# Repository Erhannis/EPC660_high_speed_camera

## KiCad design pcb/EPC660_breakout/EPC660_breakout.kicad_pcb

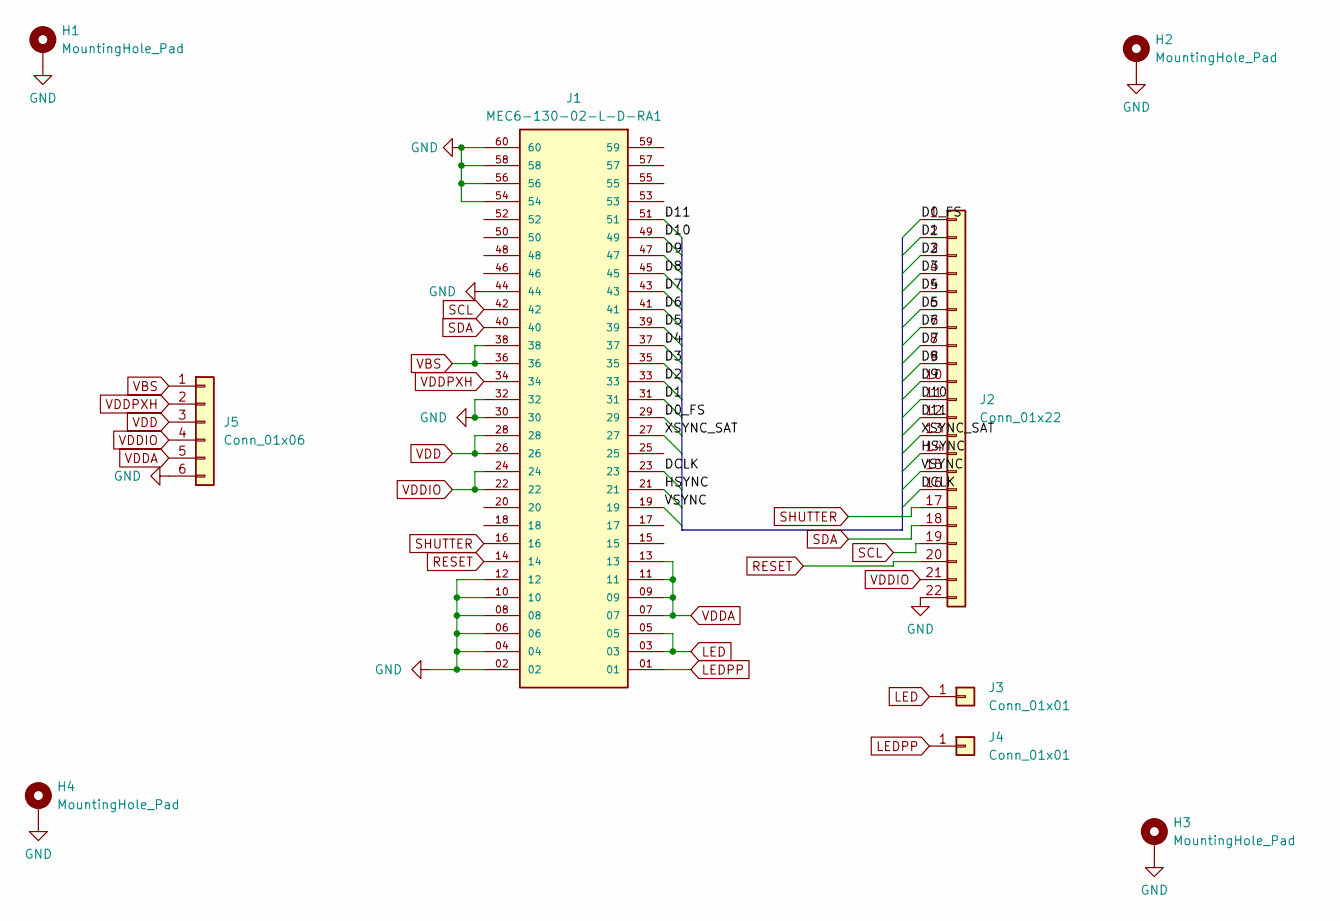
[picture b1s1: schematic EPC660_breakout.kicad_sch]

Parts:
H1, H2, H3, H4: MountingHole_Pad; MountingHole_2.5mm_Pad
J1: MEC6-130-02-L-D-RA1; SAMTEC_MEC6-130-02-L-D-RA1; PARTREV E
J2: Conn_01x22; PinHeader_1x22_P2.54mm_Vertical
J3, J4: Conn_01x01; PinHeader_1x01_P2.54mm_Vertical
J5: Conn_01x06; PinHeader_1x06_P2.54mm_Vertical

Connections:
/D0_FS: J1.29, J2.1
/D1: J1.31, J2.2
/D2: J1.33, J2.3
/D3: J1.35, J2.4
/D4: J1.37, J2.5
/D5: J1.39, J2.6
/D6: J1.41, J2.7
/D7: J1.43, J2.8
/D8: J1.45, J2.9
/D9: J1.47, J2.10
/D10: J1.49, J2.11
/D11: J1.51, J2.12
/DCLK: J1.23, J2.16
/HSYNC: J1.21, J2.14
/VSYNC: J1.19, J2.15
/XSYNC_SAT: J1.27, J2.13
GND: H1.1, H2.1, H3.1, H4.1, J1.02, J1.04, J1.06, J1.08, J1.10, J1.12, J1.30, J1.32, J1.44, J1.54, J1.56, J1.58, J1.60, J2.22, J5.6
LED: J1.03, J1.05, J3.1
LEDPP: J1.01, J4.1
RESET: J1.14, J2.20
SCL: J1.42, J2.19
SDA: J1.40, J2.18
SHUTTER: J1.16, J2.17
VBS: J1.36, J1.38, J5.1
VDD: J1.26, J1.28, J5.3
VDDA: J1.07, J1.09, J1.11, J1.13, J5.5
VDDIO: J1.22, J1.24, J2.21, J5.4
VDDPXH: J1.34, J5.2

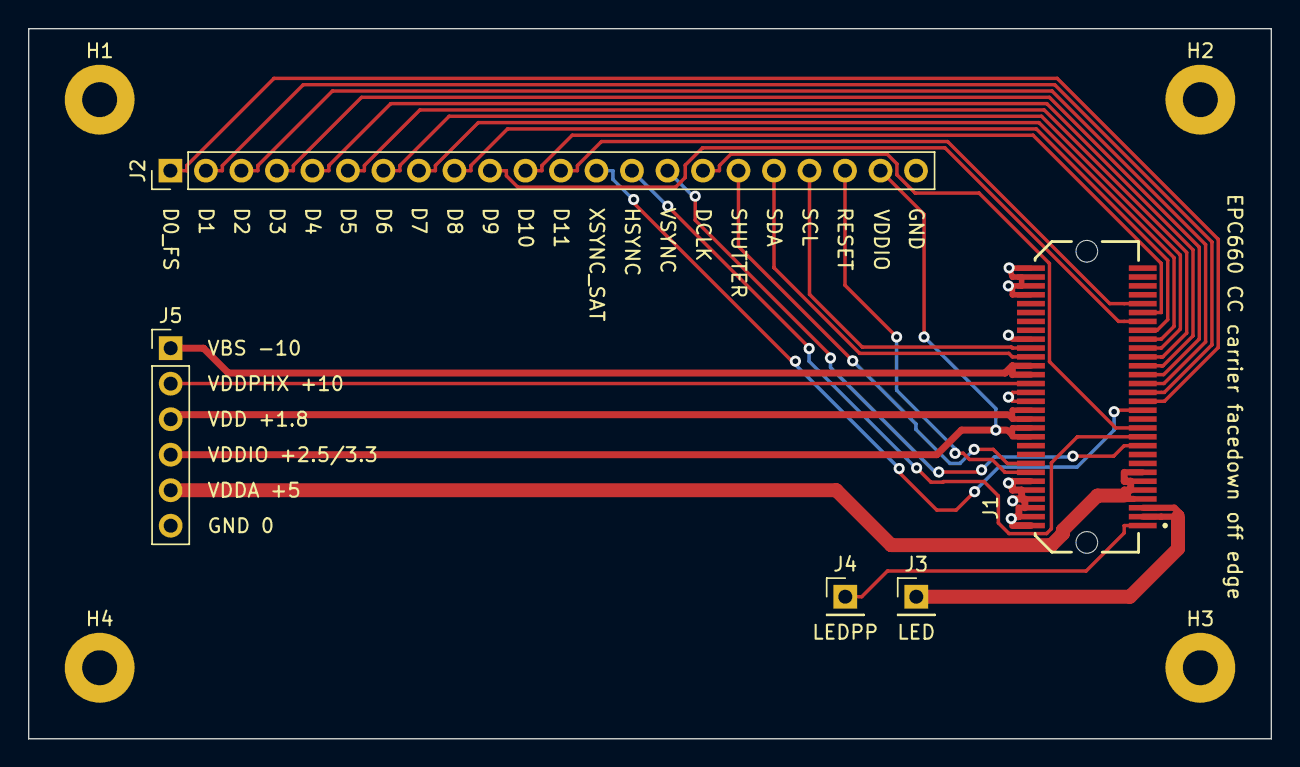
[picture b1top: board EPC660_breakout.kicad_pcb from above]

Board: 2 copper layers, 88.9 x 50.8 mm, 9 parts (0 on the bottom side), 28 nets.

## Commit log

2023-07-14 Initial commit. EPC660 CC Carrier breakout.
2023-07-14 Oh right, the ground plane.
2023-07-14 Also labels
2023-07-14 After deliberation, I increased trace widths proportional to the cardinality of the pin groups they ran to.
2023-07-14 Added bird
2023-07-14 Passes DRC
2023-07-14 Git hash
2023-07-14 OH DUH. Fixed labels.
2023-07-14 hash
2023-08-08 Frankly I forget what I did here
